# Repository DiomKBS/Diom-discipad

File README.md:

# THIS IS A FORK ORIGINAL AT https://github.com/coseyfannitutti/discipad

# discipad
 17-key numpad assembled with only through hole components, including usb type-c

[BOM, Build Guide, and Flashing Information](./doc)

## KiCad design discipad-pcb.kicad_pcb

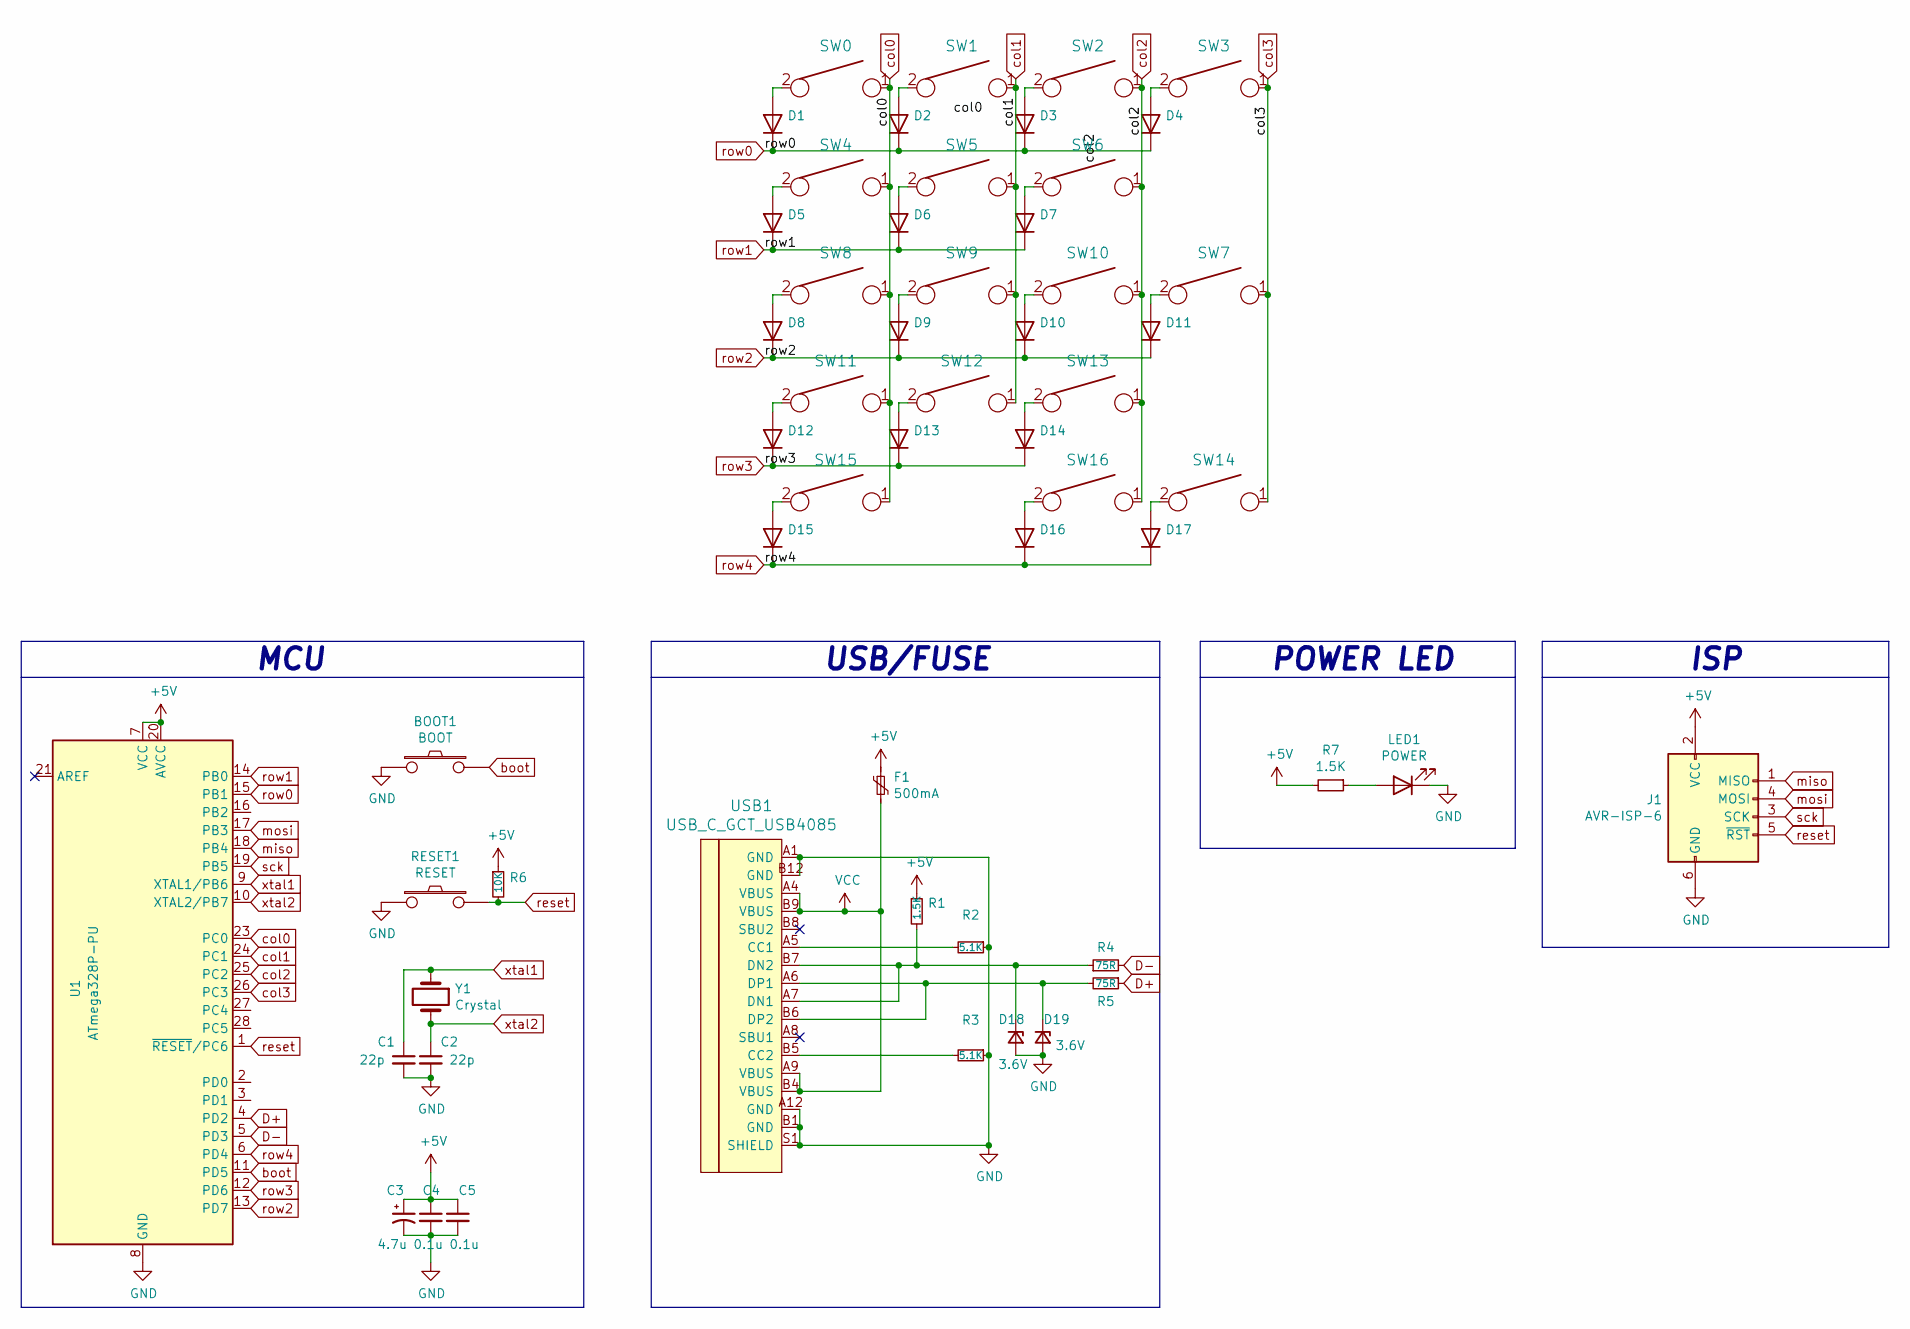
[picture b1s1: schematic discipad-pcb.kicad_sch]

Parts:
BOOT1: BOOT; SW_SPST_SKQG_WithStem
C1, C2: 22p; C_Disc_D3.0mm_W1.6mm_P2.50mm
C3: 4.7u; CP_Radial_D4.0mm_P1.50mm
C4, C5: 0.1u; C_Disc_D4.3mm_W1.9mm_P5.00mm
D1, D2, D3, D4, D5, D6, D7, D8, D9, D10, D11, D12, D13, D14, D15, D16, D17: D_DO-35_SOD27_P5.08mm_Horizontal
D18, D19: 3.6V; D_DO-35_SOD27_P5.08mm_Horizontal
F1: 500mA; polyfuse_5.1mm
J1: AVR-ISP-6; PinHeader_2x03_P2.54mm_Vertical
LED1: POWER; LED_0805_2012Metric_Pad1.15x1.40mm_HandSolder
R1, R7: 1.5K; R_Axial_DIN0204_L3.6mm_D1.6mm_P5.08mm_Horizontal
R2, R3: 5.1K; R_Axial_DIN0204_L3.6mm_D1.6mm_P5.08mm_Horizontal
R4, R5: 75R; R_Axial_DIN0204_L3.6mm_D1.6mm_P5.08mm_Horizontal
R6: 10K; R_Axial_DIN0204_L3.6mm_D1.6mm_P5.08mm_Horizontal
RESET1: RESET; SW_SPST_SKQG_WithStem
SW0, SW1, SW2, SW3, SW4, SW5, SW6, SW8, SW9, SW10, SW11, SW12, SW13, SW16: KEYSW; SW_Cherry_MX1A_1.00u_PCB-NOSCREEN
SW7, SW14: KEYSW; SW_Cherry_MX1A_2.00u_Vertical_PCB
SW15: KEYSW; SW_Cherry_MX1A_2.00u_PCB_FLIPPED
U1: ATmega328P-PU; DIP-28_W7.62mm
USB1: USB_C_GCT_USB4085; USB_C_Receptacle_GCT_USB4085
Y1: Crystal; Crystal_HC49-4H_Vertical

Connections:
+5V: C3.1, C4.1, C5.1, F1.1, J1.2 (VCC), R1.1, R6.1, R7.2, U1.7 (VCC), U1.20 (AVCC)
D+: R5.1, U1.4 (PD2)
D-: R4.2, U1.5 (PD3)
GND: BOOT1.1, C1.2, C2.2, C3.2, C4.2, C5.2, D18.2 (A), D19.2 (A), J1.6 (GND), LED1.1 (K), R2.1, R3.1, RESET1.1, U1.8 (GND), U1.22 (GND), USB1.A1 (GND), USB1.A12 (GND), USB1.B1 (GND), USB1.B12 (GND), USB1.S1 (SHIELD)
unnamed: D1.2 (A), SW0.2
unnamed: D2.2 (A), SW1.2
unnamed: D3.2 (A), SW2.2
unnamed: D4.2 (A), SW3.2
unnamed: D5.2 (A), SW4.2
unnamed: D6.2 (A), SW5.2
unnamed: D7.2 (A), SW6.2
unnamed: D8.2 (A), SW8.2
unnamed: D9.2 (A), SW9.2
unnamed: D10.2 (A), SW10.2
unnamed: D11.2 (A), SW7.2
unnamed: D12.2 (A), SW11.2
unnamed: D13.2 (A), SW12.2
unnamed: D14.2 (A), SW13.2
unnamed: D15.2 (A), SW15.2
unnamed: D16.2 (A), SW16.2
unnamed: D17.2 (A), SW14.2
unnamed: D18.1 (K), R1.2, R4.1, USB1.A7 (DN1), USB1.B7 (DN2)
unnamed: D19.1 (K), R5.2, USB1.A6 (DP1), USB1.B6 (DP2)
unnamed: LED1.2 (A), R7.1
unnamed: R2.2, USB1.A5 (CC1)
unnamed: R3.2, USB1.B5 (CC2)
VCC: F1.2, USB1.A4 (VBUS), USB1.A9 (VBUS), USB1.B4 (VBUS), USB1.B9 (VBUS)
boot: BOOT1.2, U1.11 (PD5)
col0: SW0.1, SW4.1, SW8.1, SW11.1, SW15.1, U1.23 (PC0)
col1: SW1.1, SW5.1, SW9.1, SW12.1, U1.24 (PC1)
col2: SW2.1, SW6.1, SW10.1, SW13.1, SW16.1, U1.25 (PC2)
col3: SW3.1, SW7.1, SW14.1, U1.26 (PC3)
miso: J1.1 (MISO), U1.18 (PB4)
mosi: J1.4 (MOSI), U1.17 (PB3)
reset: J1.5 (~RST), R6.2, RESET1.2, U1.1 (~RESET/PC6)
row0: D1.1 (K), D2.1 (K), D3.1 (K), D4.1 (K), U1.15 (PB1)
row1: D5.1 (K), D6.1 (K), D7.1 (K), U1.14 (PB0)
row2: D8.1 (K), D9.1 (K), D10.1 (K), D11.1 (K), U1.13 (PD7)
row3: D12.1 (K), D13.1 (K), D14.1 (K), U1.12 (PD6)
row4: D15.1 (K), D16.1 (K), D17.1 (K), U1.6 (PD4)
sck: J1.3 (SCK), U1.19 (PB5)
xtal1: C1.1, U1.9 (XTAL1/PB6), Y1.1
xtal2: C2.1, U1.10 (XTAL2/PB7), Y1.2

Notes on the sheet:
MCU
ISP
POWER LED
USB/FUSE

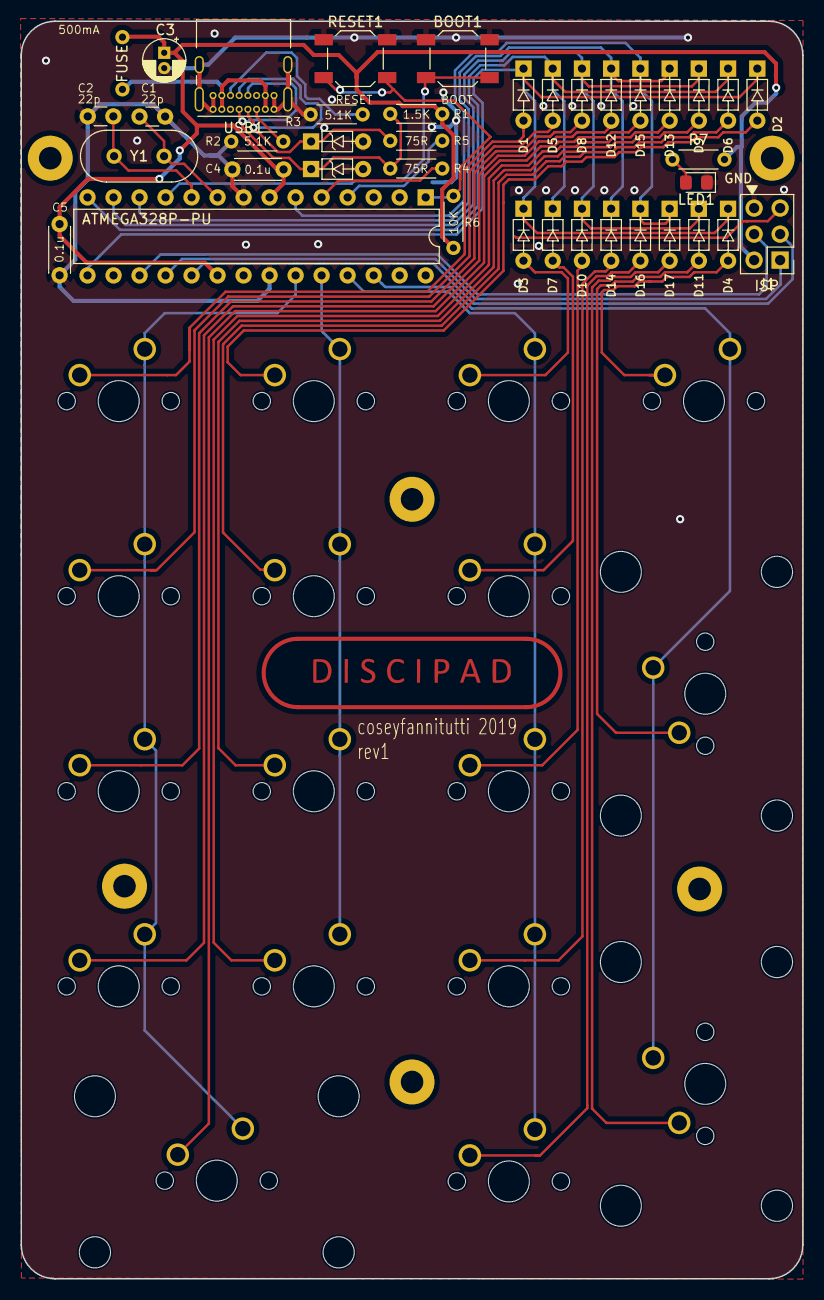
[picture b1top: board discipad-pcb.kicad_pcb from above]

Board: 2 copper layers, 76.3 x 122.8 mm, 56 parts (0 on the bottom side), 43 nets.

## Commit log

2023-08-25 version update
2023-08-25 changed button footprint
2023-08-25 added footprint to status led
2023-08-25 added avr-isp header
2023-08-25 added fuse footprint
2023-08-25 added usb-c footprint
2023-08-25 pulled new footprint to pcb
2023-08-25 changed fuse footprint
2023-08-25 integrated power led to pcb
2023-09-19 changes after drc
